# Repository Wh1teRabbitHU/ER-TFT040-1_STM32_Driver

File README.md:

# ER-TFT040-1_STM32_Driver
STM32 Driver for the ER-TFT040-1 480x800 dots 4"(3.97") color tft lcd module display with NT35510 controller

LCD Display Panel](https://www.buydisplay.com/4-inch-3-97-inch-tft-lcd-display-module-480x800-optional-touch-screen)

The driver is based on the example code, refactored to work with the Adapter. It can be used standalone or with the adapter board. For standalone usage, you can copy the following files into your own project:

- [```STM32F446_Driver/Core/Inc/er_tft040.h```](STM32F446_Driver/Core/Inc/er_tft040.h)
- [```STM32F446_Driver/Core/Src/er_tft040.c```](STM32F446_Driver/Core/Src/er_tft040.c)
- [```STM32F446_Driver/Core/Inc/font_6_12.h```](STM32F446_Driver/Core/Inc/font_6_12.h)

If you recreate the adapter, then you just need to load the Driver into STM32CubeIDE (Or in Visual Studio Code) and program the MCU. The adapter is using a STM32F030R8T6 MCU, but you can replace it with any other STM32 if you want to extend the adapter. The only requirement is that you follow the pinout and connect them the same way as in the original design.

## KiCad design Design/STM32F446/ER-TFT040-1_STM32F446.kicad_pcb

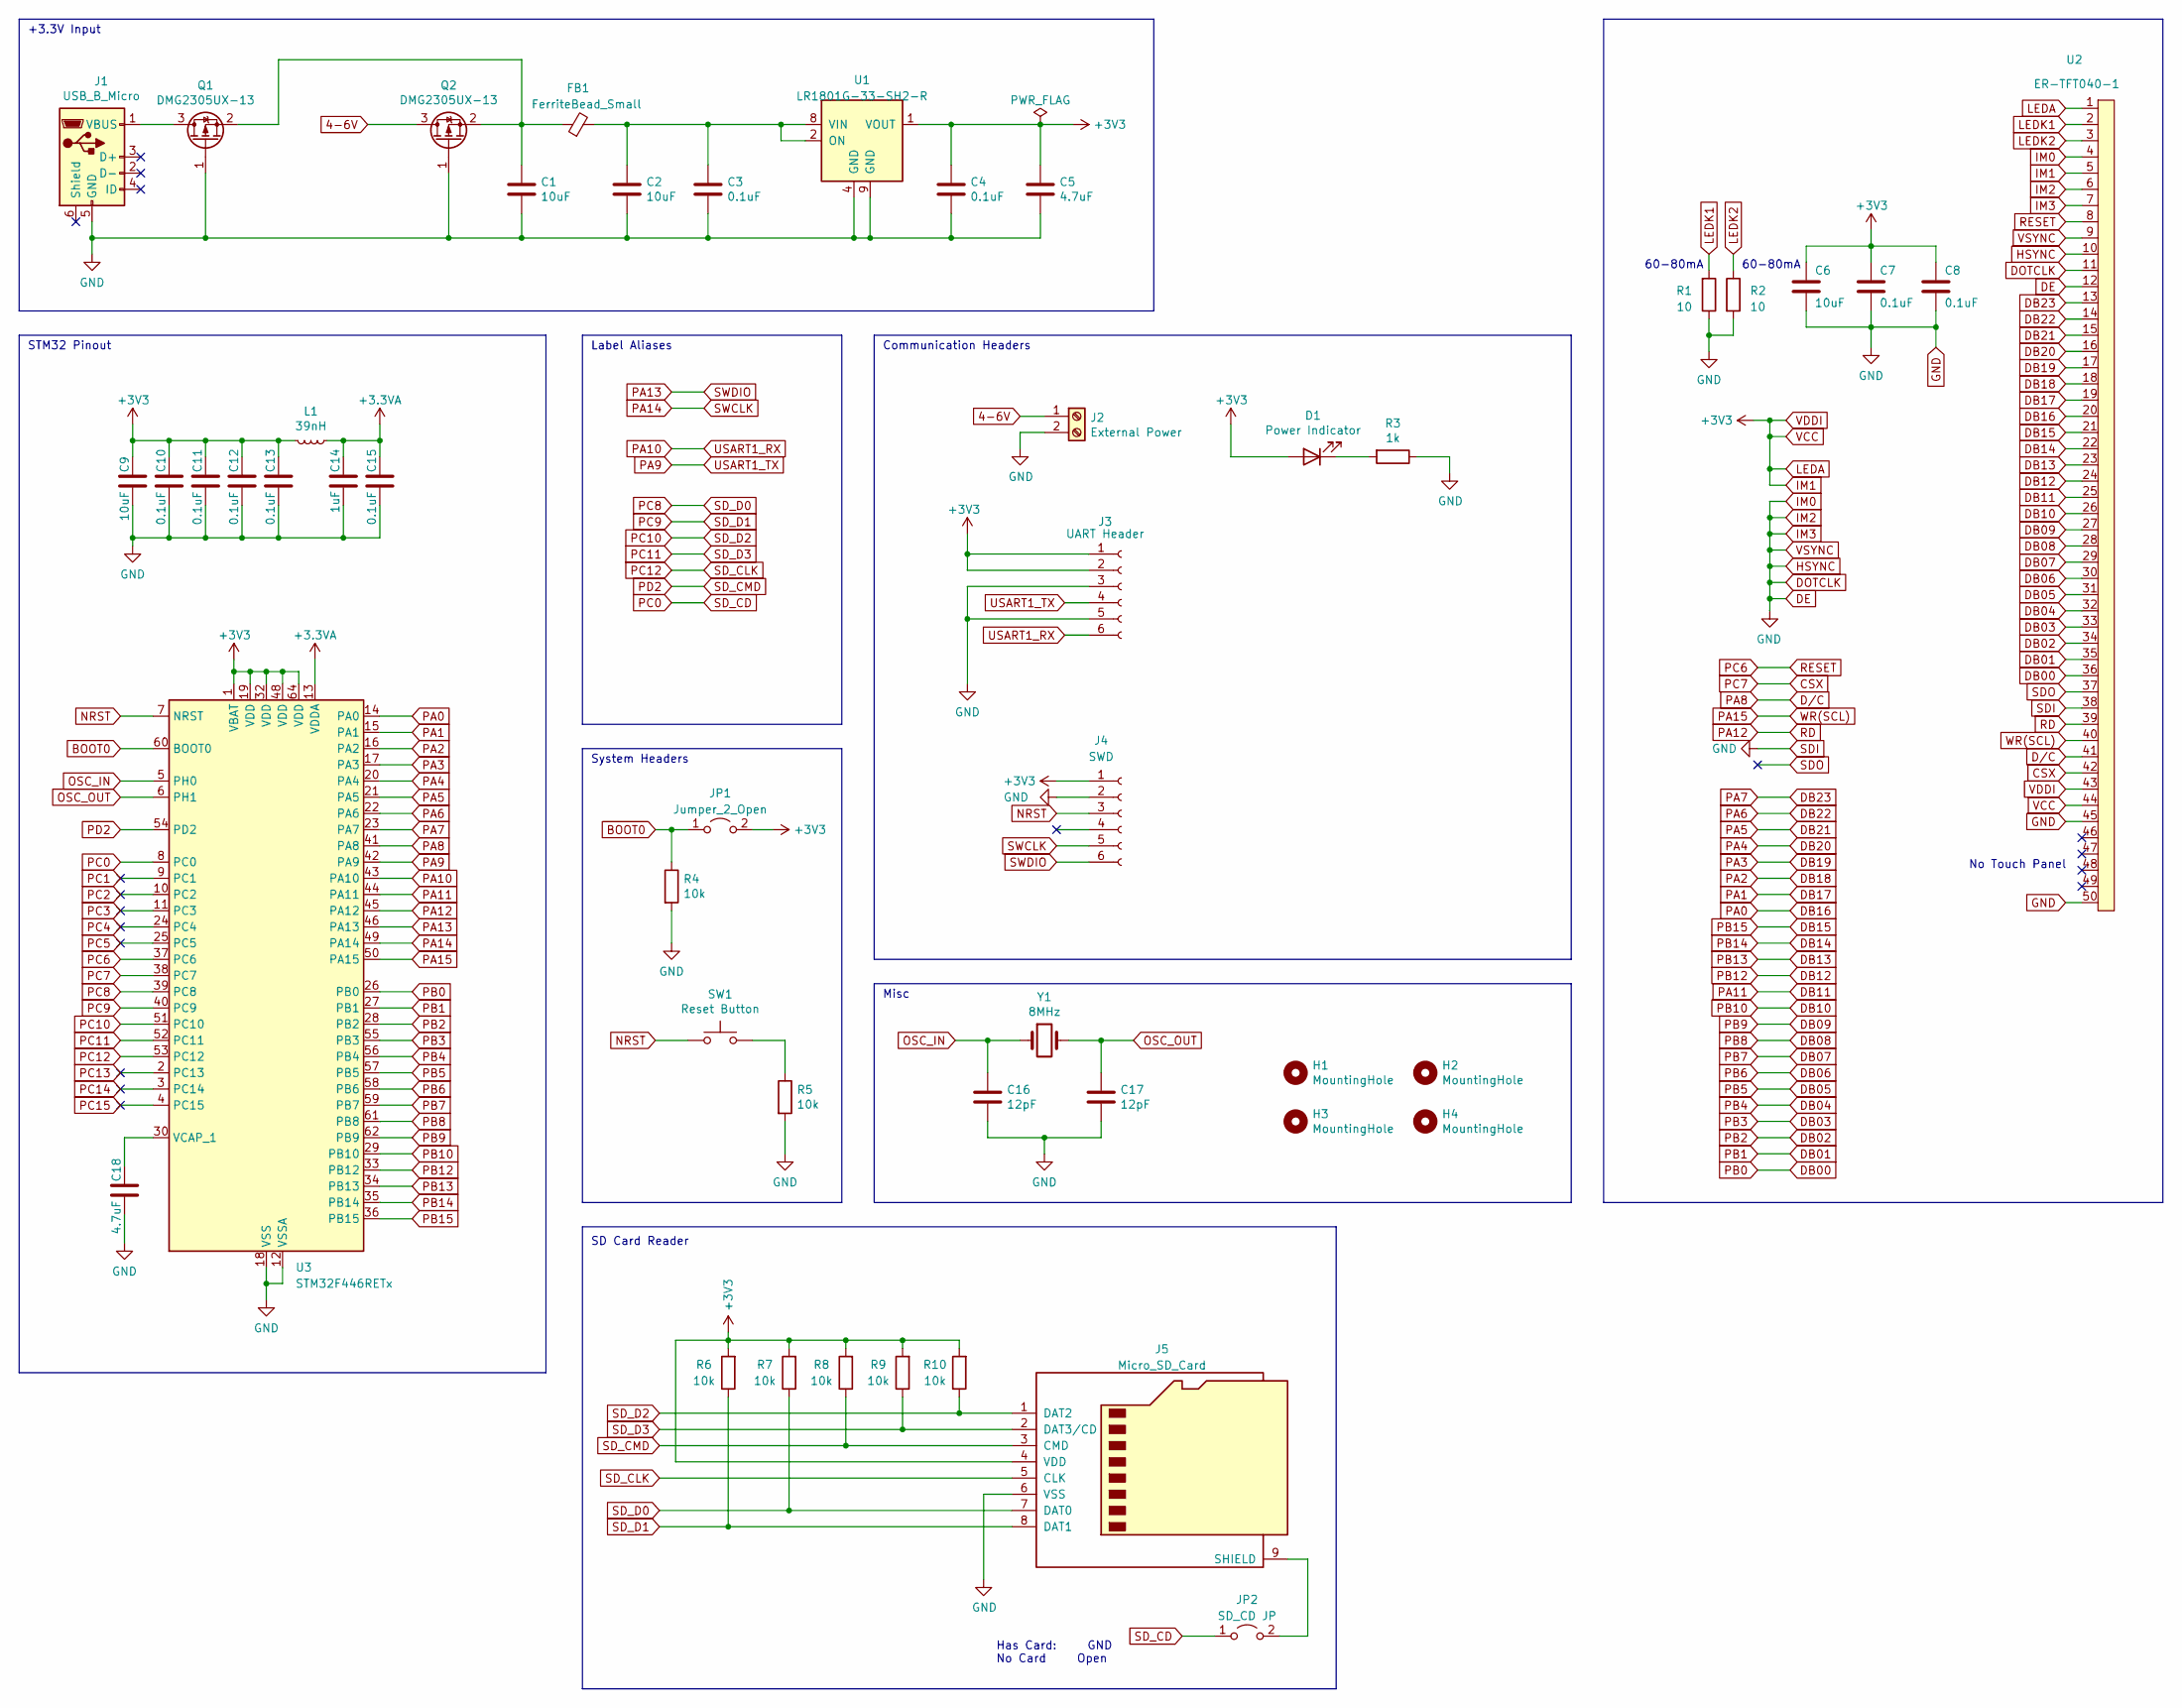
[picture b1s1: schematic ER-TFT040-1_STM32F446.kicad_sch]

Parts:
C1, C2, C6, C9: 10uF; C_0805_2012Metric
C3, C4, C7, C8, C10, C11, C12, C13, C15: 0.1uF; C_0805_2012Metric
C5, C18: 4.7uF; C_0805_2012Metric
C14: 1uF; C_0805_2012Metric
C16, C17: 12pF; C_0805_2012Metric
D1: Power Indicator; LED_0603_1608Metric
FB1: FerriteBead_Small; L_0805_2012Metric
H1, H2, H3, H4: MountingHole; MountingHole_3mm_Pad_Via
J1: USB_B_Micro; Micro_USB_B_Female
J2: External Power; JST_XH_B2B-XH-A_1x02_P2.50mm_Vertical
J3: UART Header; AFA07-S06FCA-00
J4: SWD; AFA07-S06FCA-00
J5: Micro_SD_Card; MicroSD-TF-015
JP1: Jumper_2_Open; SolderJumper-2_P1.3mm_Open_RoundedPad1.0x1.5mm
JP2: SD_CD JP; SolderJumper-2_P1.3mm_Open_RoundedPad1.0x1.5mm
L1: 39nH; L_0805_2012Metric
Q1, Q2: DMG2305UX-13; SOT-23
R1, R2: 10; R_1206_3216Metric
R3: 1k; R_1206_3216Metric
R4, R5, R6, R7, R8, R9, R10: 10k; R_1206_3216Metric
SW1: Reset Button; SW_SPST_TL3342
U1: LR1801G-33-SH2-R
U2: ER-TFT040-1; FFC2B17-50-T
U3: STM32F446RETx; LQFP-64_10x10mm_P0.5mm
Y1: 8MHz; Crystal_SMD_HC49-SD

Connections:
4-6V: J2.1, Q2.3 (D)
+3V3: C4.1, C5.1, C6.1, C7.1, C8.1, C9.1, C10.1, C11.1, C12.1, C13.1, D1.2 (A), J3.1, J3.2, J4.1, J5.4 (VDD), JP1.2 (B), L1.2, R6.2, R7.2, R8.2, R9.2, R10.2, U1.1 (VOUT), U2.1, U2.5, U2.43, U2.44, U3.1 (VBAT), U3.19 (VDD), U3.32 (VDD), U3.48 (VDD), U3.64 (VDD)
+3V3A: C14.1, C15.1, L1.1, U3.13 (VDDA)
BOOT0: JP1.1 (A), R4.1, U3.60 (BOOT0)
CSX: U2.42, U3.38 (PC7)
DB00: U2.36, U3.26 (PB0)
DB01: U2.35, U3.27 (PB1)
DB02: U2.34, U3.28 (PB2)
DB03: U2.33, U3.55 (PB3)
DB04: U2.32, U3.56 (PB4)
DB05: U2.31, U3.57 (PB5)
DB06: U2.30, U3.58 (PB6)
DB07: U2.29, U3.59 (PB7)
DB08: U2.28, U3.61 (PB8)
DB09: U2.27, U3.62 (PB9)
DB10: U2.26, U3.29 (PB10)
DB11: U2.25, U3.44 (PA11)
DB12: U2.24, U3.33 (PB12)
DB13: U2.23, U3.34 (PB13)
DB14: U2.22, U3.35 (PB14)
DB15: U2.21, U3.36 (PB15)
DB16: U2.20, U3.14 (PA0)
DB17: U2.19, U3.15 (PA1)
DB18: U2.18, U3.16 (PA2)
DB19: U2.17, U3.17 (PA3)
DB20: U2.16, U3.20 (PA4)
DB21: U2.15, U3.21 (PA5)
DB22: U2.14, U3.22 (PA6)
DB23: U2.13, U3.23 (PA7)
D/C: U2.41, U3.41 (PA8)
GND: C1.2, C2.2, C3.2, C4.2, C5.2, C6.2, C7.2, C8.2, C9.2, C10.2, C11.2, C12.2, C13.2, C14.2, C15.2, C16.2, C17.2, C18.2, J1.5 (GND), J2.2, J3.3, J3.5, J4.2, J5.6 (VSS), Q1.1 (G), Q2.1 (G), R1.1, R2.2, R3.1, R4.2, R5.2, U1.4 (GND), U1.9 (GND), U2.4, U2.6, U2.7, U2.9, U2.10, U2.11, U2.12, U2.38, U2.45, U2.50, U3.12 (VSSA), U3.18 (VSS), U3.31 (VSS), U3.47 (VSS), U3.63 (VSS)
LEDK1: R1.2, U2.2
LEDK2: R2.1, U2.3
NRST: J4.3, SW1.1, U3.7 (NRST)
unnamed: D1.1 (K), R3.2
unnamed: J1.1 (VBUS), Q1.3 (D)
unnamed: J5.9 (SHIELD), JP2.2 (B)
unnamed: C1.1, FB1.1, Q1.2 (S), Q2.2 (S)
unnamed: R5.1, SW1.2
unnamed: C2.1, C3.1, FB1.2, U1.2 (ON), U1.8 (VIN)
unnamed: C18.1, U3.30 (VCAP_1)
OSC_IN: C16.1, U3.5 (PH0), Y1.1
OSC_OUT: C17.1, U3.6 (PH1), Y1.2
PA9: J3.4, U3.42 (PA9)
PA10: J3.6, U3.43 (PA10)
PA12: U2.39, U3.45 (PA12)
PA13: J4.6, U3.46 (PA13)
PA14: J4.5, U3.49 (PA14)
PA15: U2.40, U3.50 (PA15)
PC0: JP2.1 (A), U3.8 (PC0)
PC1: U3.9 (PC1)
PC2: U3.10 (PC2)
PC3: U3.11 (PC3)
PC4: U3.24 (PC4)
PC5: U3.25 (PC5)
PC6: U2.8, U3.37 (PC6)
PC8: J5.7 (DAT0), R7.1, U3.39 (PC8)
PC9: J5.8 (DAT1), R6.1, U3.40 (PC9)
PC10: J5.1 (DAT2), R10.1, U3.51 (PC10)
PC11: J5.2 (DAT3/CD), R9.1, U3.52 (PC11)
PC12: J5.5 (CLK), U3.53 (PC12)
PC13: U3.2 (PC13)
PC14: U3.3 (PC14)
PC15: U3.4 (PC15)
PD2: J5.3 (CMD), R8.1, U3.54 (PD2)
SDO: U2.37

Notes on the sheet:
Misc
60-80mA
+3.3V Input
System Headers
No Touch Panel
Has Card: GND No Card Open
Label Aliases
SD Card Reader
Communication Headers
STM32 Pinout

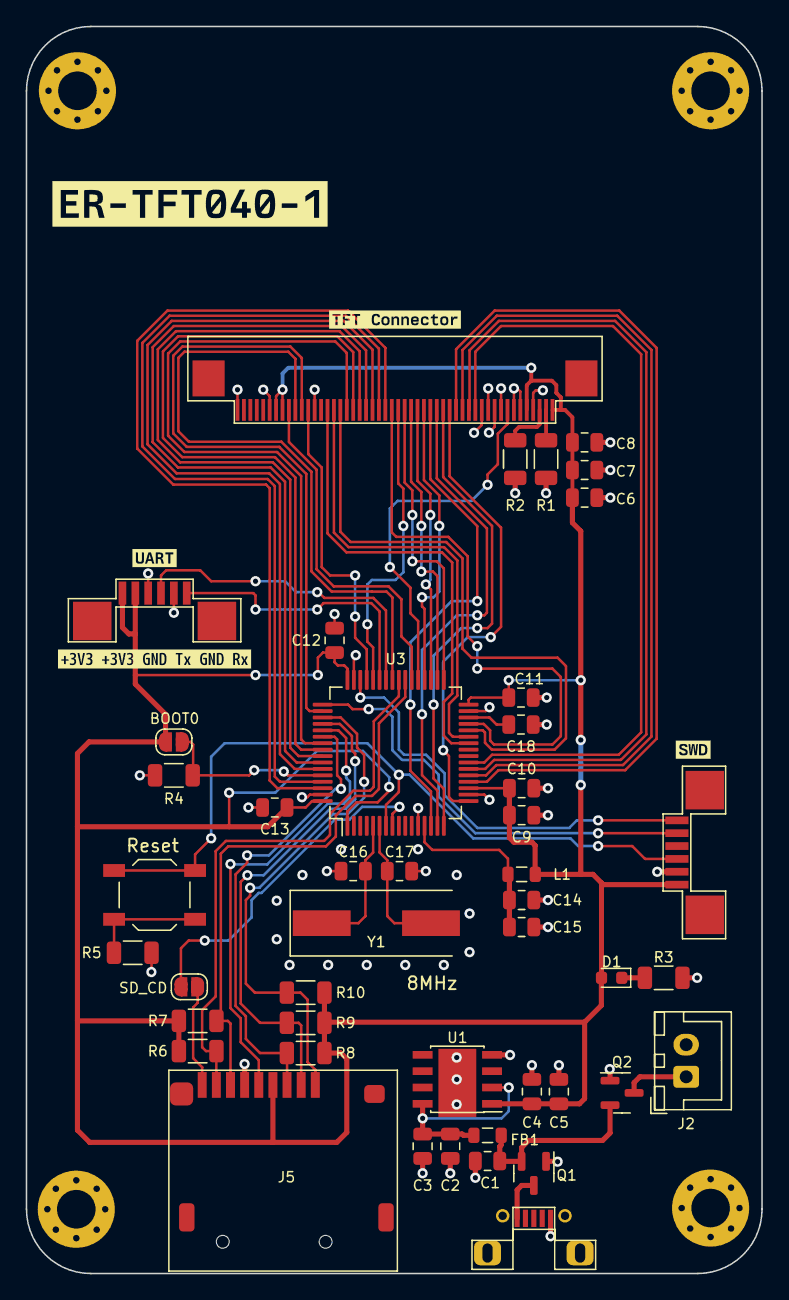
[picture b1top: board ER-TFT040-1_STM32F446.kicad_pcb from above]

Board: 4 copper layers, 57.2 x 97.0 mm, 54 parts (0 on the bottom side), 57 nets.

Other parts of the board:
kibuzzard-653E05A6: G***; kibuzzard-653E05A6
kibuzzard-653E05C0: G***; kibuzzard-653E05C0
kibuzzard-653E07B4: G***; kibuzzard-653E07B4
kibuzzard-653E062C: G***; kibuzzard-653E062C
kibuzzard-653E0743: G***; kibuzzard-653E0743

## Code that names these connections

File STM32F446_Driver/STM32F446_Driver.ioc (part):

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Mcu.Name=STM32F446R(C-E)Tx
Mcu.Package=LQFP64
Mcu.UserName=STM32F446RETx
PA0-WKUP.GPIOParameters=GPIO_Label
PA0-WKUP.GPIO_Label=DISPLAY_D16
PA0-WKUP.Signal=GPIO_Output
PA1.GPIOParameters=GPIO_Label
PA1.GPIO_Label=DISPLAY_D17
PA1.Signal=GPIO_Output
PA10.Mode=Asynchronous
PA10.Signal=USART1_RX
PA11.GPIOParameters=GPIO_Label
PA11.GPIO_Label=DISPLAY_D11
PA11.Signal=GPIO_Output
PA12.GPIOParameters=GPIO_Label
PA12.GPIO_Label=DISPLAY_RD
PA12.Signal=GPIO_Output
PA13.Mode=Serial_Wire
PA13.Signal=SYS_JTMS-SWDIO
PA14.Mode=Serial_Wire
PA14.Signal=SYS_JTCK-SWCLK
PA15.GPIOParameters=GPIO_Label
PA15.GPIO_Label=DISPLAY_WR
PA15.Signal=GPIO_Output
PA2.GPIOParameters=GPIO_Label
PA2.GPIO_Label=DISPLAY_D18
PA2.Signal=GPIO_Output
PA3.GPIOParameters=GPIO_Label
PA3.GPIO_Label=DISPLAY_D19
PA3.Signal=GPIO_Output
PA4.GPIOParameters=GPIO_Label
PA4.GPIO_Label=DISPLAY_D20
PA4.Signal=GPIO_Output
PA5.GPIOParameters=GPIO_Label
PA5.GPIO_Label=DISPLAY_D21
PA5.Signal=GPIO_Output
PA6.GPIOParameters=GPIO_Label
PA6.GPIO_Label=DISPLAY_D22
PA6.Signal=GPIO_Output
PA7.GPIOParameters=GPIO_Label
PA7.GPIO_Label=DISPLAY_D23
PA7.Signal=GPIO_Output
PA8.GPIOParameters=GPIO_Label
PA8.GPIO_Label=DISPLAY_DC
PA8.Signal=GPIO_Output
PA9.Mode=Asynchronous
PA9.Signal=USART1_TX
PB0.GPIOParameters=GPIO_Label
PB0.GPIO_Label=DISPLAY_D0
PB0.Signal=GPIO_Output
PB1.GPIOParameters=GPIO_Label
PB1.GPIO_Label=DISPLAY_D1
PB1.Signal=GPIO_Output
PB10.GPIOParameters=GPIO_Label
PB10.GPIO_Label=DISPLAY_D10
PB10.Signal=GPIO_Output
PB12.GPIOParameters=GPIO_Label
PB12.GPIO_Label=DISPLAY_D12
PB12.Signal=GPIO_Output
PB13.GPIOParameters=GPIO_Label
PB13.GPIO_Label=DISPLAY_D13
PB13.Signal=GPIO_Output
PB14.GPIOParameters=GPIO_Label
PB14.GPIO_Label=DISPLAY_D14
PB14.Signal=GPIO_Output
PB15.GPIOParameters=GPIO_Label
PB15.GPIO_Label=DISPLAY_D15
PB15.Signal=GPIO_Output
PB2.GPIOParameters=GPIO_Label
PB2.GPIO_Label=DISPLAY_D2
PB2.Signal=GPIO_Output
PB3.GPIOParameters=GPIO_Label
PB3.GPIO_Label=DISPLAY_D3
PB3.Signal=GPIO_Output
PB4.GPIOParameters=GPIO_Label
PB4.GPIO_Label=DISPLAY_D4
PB4.Signal=GPIO_Output
PB5.GPIOParameters=GPIO_Label
PB5.GPIO_Label=DISPLAY_D5
PB5.Signal=GPIO_Output
PB6.GPIOParameters=GPIO_Label
PB6.GPIO_Label=DISPLAY_D6
PB6.Signal=GPIO_Output
PB7.GPIOParameters=GPIO_Label
PB7.GPIO_Label=DISPLAY_D7
PB7.Signal=GPIO_Output
PB8.GPIOParameters=GPIO_Label
PB8.GPIO_Label=DISPLAY_D8
PB8.Signal=GPIO_Output
PB9.GPIOParameters=GPIO_Label
PB9.GPIO_Label=DISPLAY_D9
PB9.Signal=GPIO_Output
PC0.GPIOParameters=GPIO_PuPd,GPIO_Label
PC0.GPIO_Label=SD_CD
PC0.GPIO_PuPd=GPIO_NOPULL
PC0.Signal=GPIO_Input
PC10.Mode=SD_4_bits_Wide_bus
PC10.Signal=SDIO_D2
PC11.Mode=SD_4_bits_Wide_bus
PC11.Signal=SDIO_D3
PC12.Mode=SD_4_bits_Wide_bus
PC12.Signal=SDIO_CK
PC6.GPIOParameters=GPIO_Label
PC6.GPIO_Label=DISPLAY_RESET
PC6.Signal=GPIO_Output
PC7.GPIOParameters=GPIO_Label
PC7.GPIO_Label=DISPLAY_CSX
PC7.Signal=GPIO_Output
PC8.Mode=SD_4_bits_Wide_bus
PC8.Signal=SDIO_D0
PC9.Mode=SD_4_bits_Wide_bus
PC9.Signal=SDIO_D1
PD2.Mode=SD_4_bits_Wide_bus
PD2.Signal=SDIO_CMD
PH0-OSC_IN.Mode=HSE-External-Oscillator
PH0-OSC_IN.Signal=RCC_OSC_IN
PH1-OSC_OUT.Mode=HSE-External-Oscillator
PH1-OSC_OUT.Signal=RCC_OSC_OUT
RCC.HSE_VALUE=8000000
RCC.SYSCLKFreq_VALUE=90000000
RCC.SYSCLKSource=RCC_SYSCLKSOURCE_PLLCLK
board=custom

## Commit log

2023-03-04 Adding default STM32 Project files with initial pinout configuration
2023-03-04 Removing SPI pins
2023-03-04 Changing USART to UART
2023-08-20 Add Generated codes and base implementation
2023-08-20 Refactoring base code
2023-08-20 Refactor
2023-08-20 Remove output folder
2023-08-20 No more build files
2023-08-20 Finalise the library and update the readme
2023-08-20 Add further helper functions
2023-08-21 Add more functions
2023-08-21 Removing drawFastVLine
2023-10-03 Adding STM32F446 base drivers
2023-10-03 Renaming driver folder
2024-01-07 STM32F446 - Adding display driver
2024-01-07 STM32F446 - Adding display test code
2024-01-07 STM32F446 - Making it 24 bit with 16mil colors
2024-01-07 Working image readSTM32F446 - Working image read and display
2024-01-08 Fixing color scheme
2024-01-08 Simplifying the code and exclude progressive mode jpegs
2024-01-08 Simplifying the code even further
2024-01-08 Significantly speed up the picture drawing + cleaning up the code
2024-01-08 Further code cleanup
2025-02-02 Adding the design files to the project
2025-02-11 Fixing links in the README.md file
